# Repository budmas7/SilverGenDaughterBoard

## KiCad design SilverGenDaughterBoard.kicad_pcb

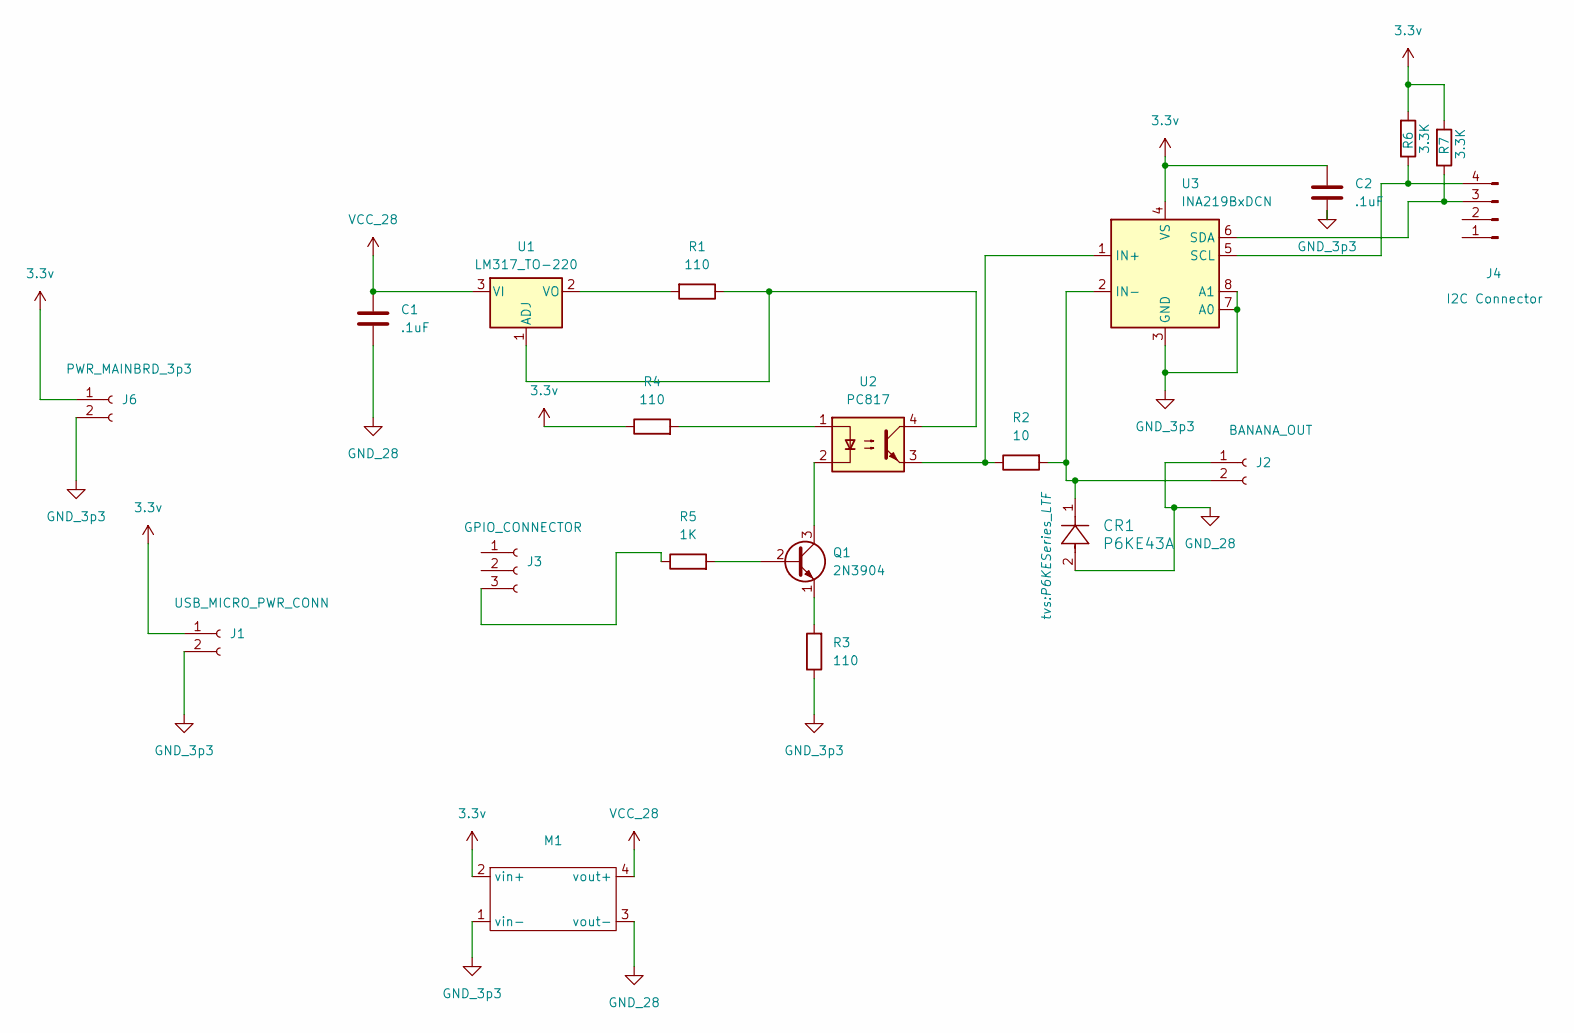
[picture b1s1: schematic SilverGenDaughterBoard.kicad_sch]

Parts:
C1, C2: .1uF; C_Disc_D5.1mm_W3.2mm_P5.00mm
CR1: P6KE43A; P6KESeries_LTF
J1: USB_MICRO_PWR_CONN; JST_PH_B2B-PH-K_1x02_P2.00mm_Vertical
J2: BANANA_OUT; JST_PH_B2B-PH-K_1x02_P2.00mm_Vertical
J3: GPIO_CONNECTOR; JST_PH_B3B-PH-K_1x03_P2.00mm_Vertical
J4: I2C Connector; JST_PH_B4B-PH-K_1x04_P2.00mm_Vertical
J6: PWR_MAINBRD_3p3; JST_PH_B2B-PH-K_1x02_P2.00mm_Vertical
M1: CMT3608_PWR_MODULE_w_USB
Q1: 2N3904; TO-92_Inline
R1, R3, R4: 110; R_Axial_DIN0207_L6.3mm_D2.5mm_P7.62mm_Horizontal
R2: 10; R_Axial_DIN0207_L6.3mm_D2.5mm_P7.62mm_Horizontal
R5: 1K; R_Axial_DIN0207_L6.3mm_D2.5mm_P7.62mm_Horizontal
R6, R7: 3.3K; R_Axial_DIN0207_L6.3mm_D2.5mm_P7.62mm_Horizontal
U1: LM317_TO-220; TO-220-3_Vertical
U2: PC817; DIP-4_W7.62mm
U3: INA219BxDCN; SOT-23-8

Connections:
3.3v: C2.1, J1.1, J6.1, M1.2 (vin+), R4.1, R6.2, R7.2, U3.4 (VS)
GND_3p3: C2.2, J1.2, J6.2, M1.1 (vin-), R3.1, U3.3 (GND), U3.7 (A0), U3.8 (A1)
GND_28: C1.2, CR1.2, J2.1, M1.3 (vout-)
unnamed: CR1.1, J2.2, R2.2, U3.2 (IN-)
unnamed: J3.3, R5.1
unnamed: J4.3, R7.1, U3.6 (SDA)
unnamed: J4.4, R6.1, U3.5 (SCL)
unnamed: Q1.2 (B), R5.2
unnamed: Q1.3 (C), U2.2
unnamed: Q1.1 (E), R3.2
unnamed: R4.2, U2.1
unnamed: R1.1, U1.1 (ADJ), U2.4
unnamed: R1.2, U1.2 (VO)
unnamed: R2.1, U2.3, U3.1 (IN+)
VCC_28: C1.1, M1.4 (vout+), U1.3 (VI)

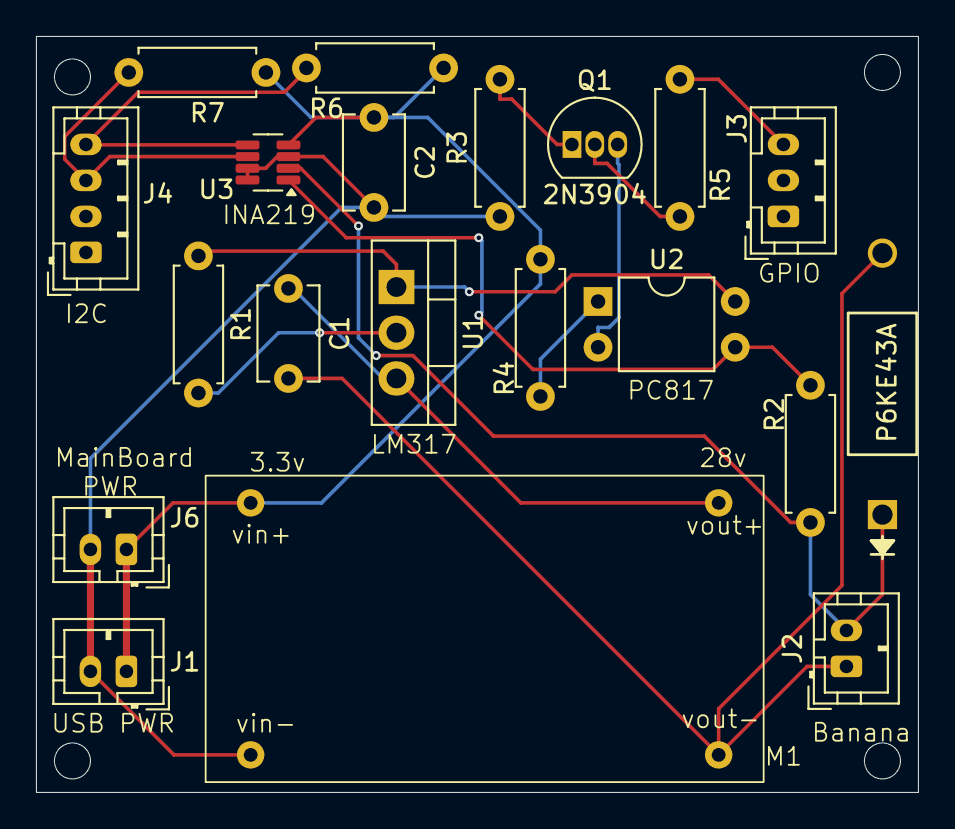
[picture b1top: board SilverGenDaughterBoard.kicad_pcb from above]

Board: 2 copper layers, 49.0 x 42.0 mm, 20 parts (0 on the bottom side), 15 nets.

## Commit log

2024-12-30 Initial commit of rev 0.2
